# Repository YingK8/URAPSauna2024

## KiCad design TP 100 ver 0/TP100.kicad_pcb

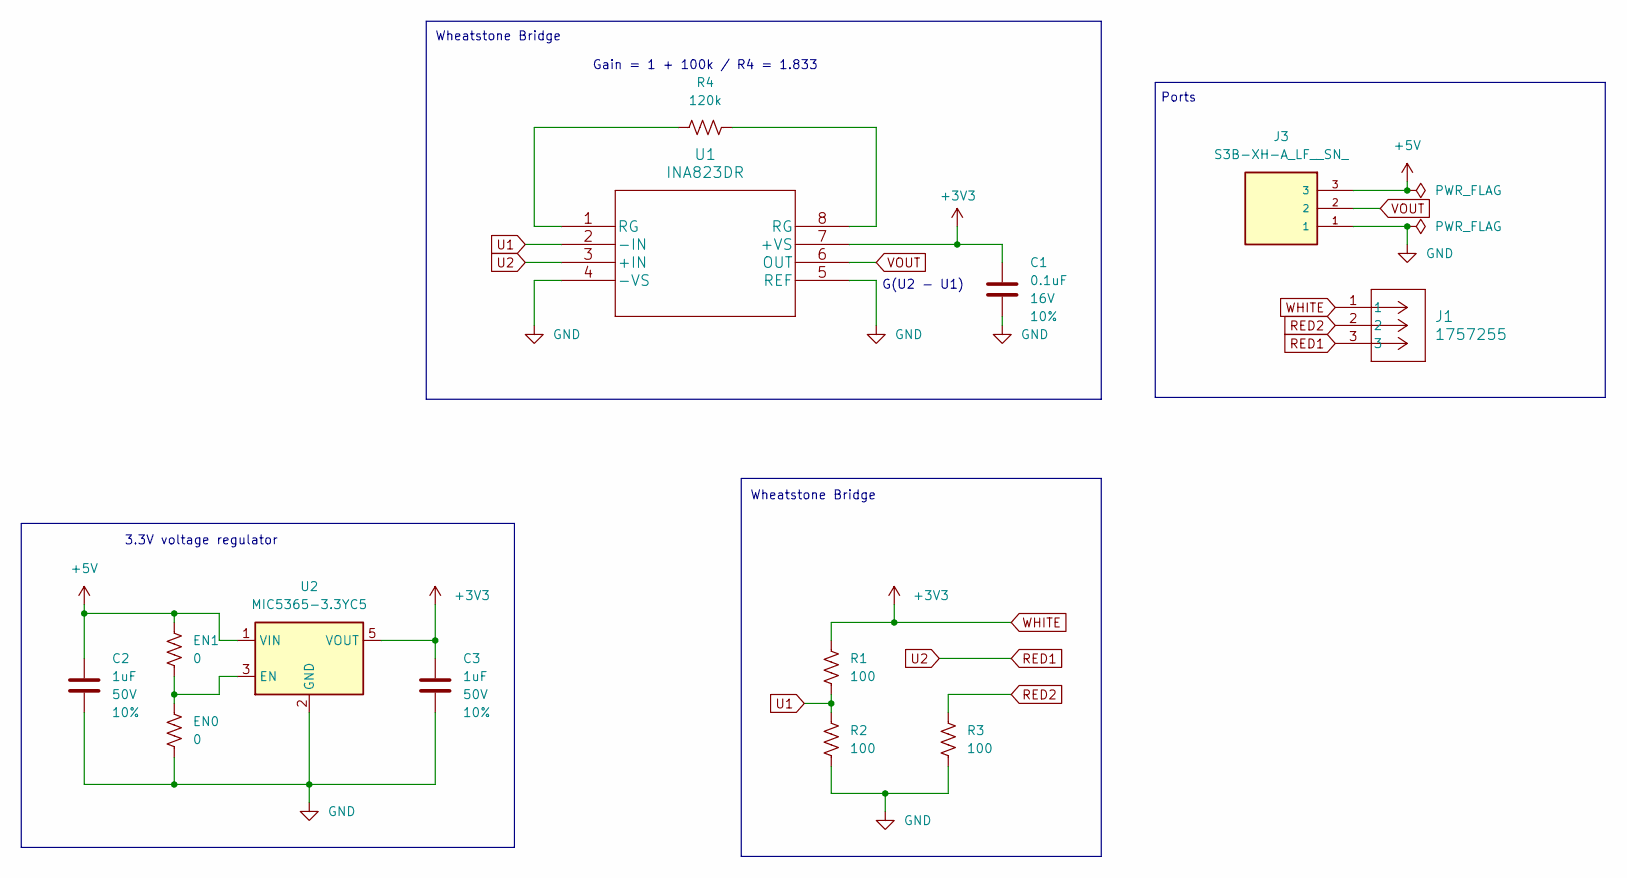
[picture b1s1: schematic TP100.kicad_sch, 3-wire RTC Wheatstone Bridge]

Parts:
C1: 0.1uF; C_0603_1608Metric_Pad1.08x0.95mm_HandSolder; Voltage 16V; Tolerance 10%
C2, C3: 1uF; C_0603_1608Metric_Pad1.08x0.95mm_HandSolder; Voltage 50V; Tolerance 10%
EN0, EN1: 0; C_0603_1608Metric_Pad1.08x0.95mm_HandSolder
J1: 1757255; PhoenixContact_MSTBA_2,5_3-G-5,08_1x03_P5.08mm_Horizontal
J3: S3B-XH-A_LF__SN_; JST_S3B-XH-A_LF__SN_; PARTREV N/A
R1, R2, R3: 100; R_0603_1608Metric_Pad0.98x0.95mm_HandSolder
R4: 120k; R_0603_1608Metric_Pad0.98x0.95mm_HandSolder
U1: INA823DR; INA823DT
U2: MIC5365-3.3YC5; SOT-353_SC-70-5_Handsoldering

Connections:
+5V: C2.1, EN1.2, J3.3, U2.1 (VIN)
GND: C1.2, C2.2, C3.2, EN0.1, J3.1, R2.2, R3.2, U1.4 (-VS), U1.5 (REF), U2.2 (GND)
unnamed: R4.1, U1.1 (RG)
unnamed: R4.2, U1.8 (RG)
unnamed: EN0.2, EN1.1, U2.3 (EN)
RED1: J1.3, U1.3 (+IN)
RED2: J1.2, R3.1
U1: R1.2, R2.1, U1.2 (-IN)
VOUT: J3.2, U1.6 (OUT)
WHITE: C1.1, C3.1, J1.1, R1.1, U1.7 (+VS), U2.5 (VOUT)

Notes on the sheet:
Wheatstone Bridge
Gain = 1 + 100k / R4 = 1.833
Ports
3.3V voltage regulator
G(U2 - U1)

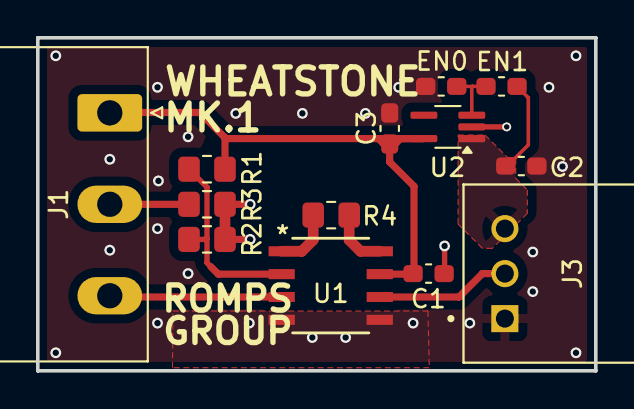
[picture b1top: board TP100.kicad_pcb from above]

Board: 2 copper layers, 31.0 x 18.5 mm, 13 parts (0 on the bottom side), 10 nets.

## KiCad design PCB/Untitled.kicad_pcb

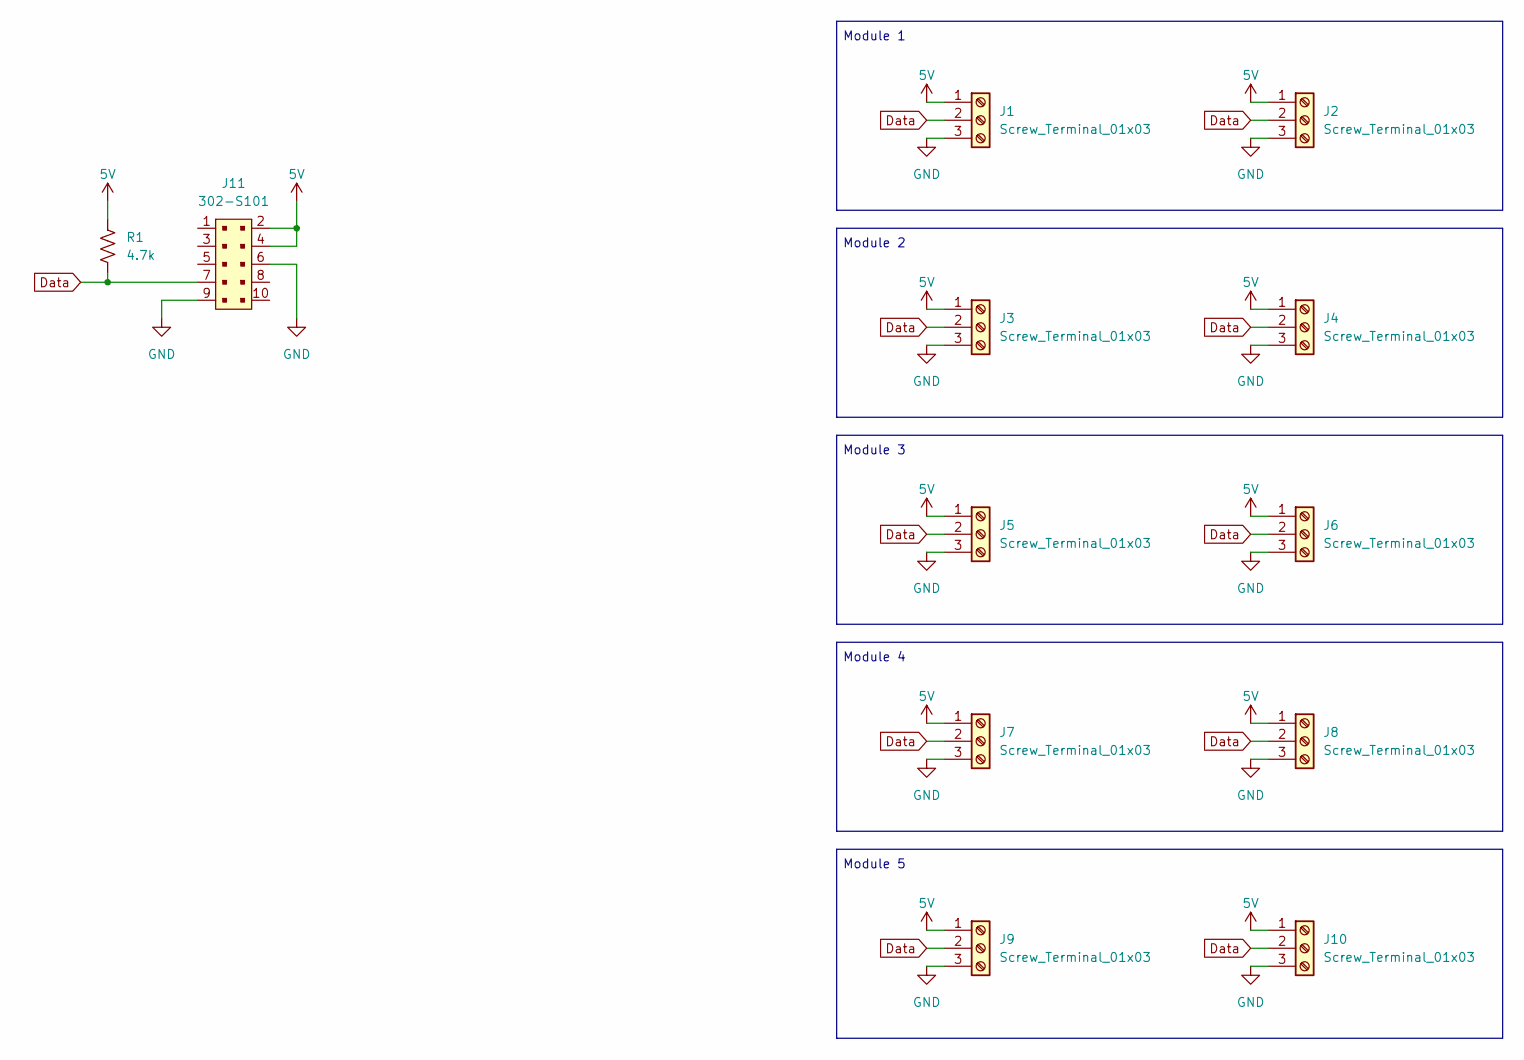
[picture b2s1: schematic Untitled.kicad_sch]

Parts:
J1, J2, J3, J4, J5, J6, J7, J8, J9, J10: Screw_Terminal_01x03; TerminalBlock_Xinya_XY308-2.54-3P_1x03_P2.54mm_Horizontal
J11: 302-S101; PinHeader_2x5_P2.54mm_Drill1.2mm; MPN 302-S101; Digi-Key_PN ED1543-ND
R1: 4.7k; R_Axial_DIN0207_L6.3mm_D2.5mm_P10.16mm_Horizontal

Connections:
5V: J1.1, J2.1, J3.1, J4.1, J5.1, J6.1, J7.1, J8.1, J9.1, J10.1, J11.2, J11.4, R1.1
Data: J1.2, J2.2, J3.2, J4.2, J5.2, J6.2, J7.2, J8.2, J9.2, J10.2, J11.7, R1.2
GND: J1.3, J2.3, J3.3, J4.3, J5.3, J6.3, J7.3, J8.3, J9.3, J10.3, J11.6, J11.9

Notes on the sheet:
Module 2
Module 3
Module 5
Module 4
Module 1

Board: 2 copper layers, 12 parts (0 on the bottom side), 3 nets, no tracks yet.

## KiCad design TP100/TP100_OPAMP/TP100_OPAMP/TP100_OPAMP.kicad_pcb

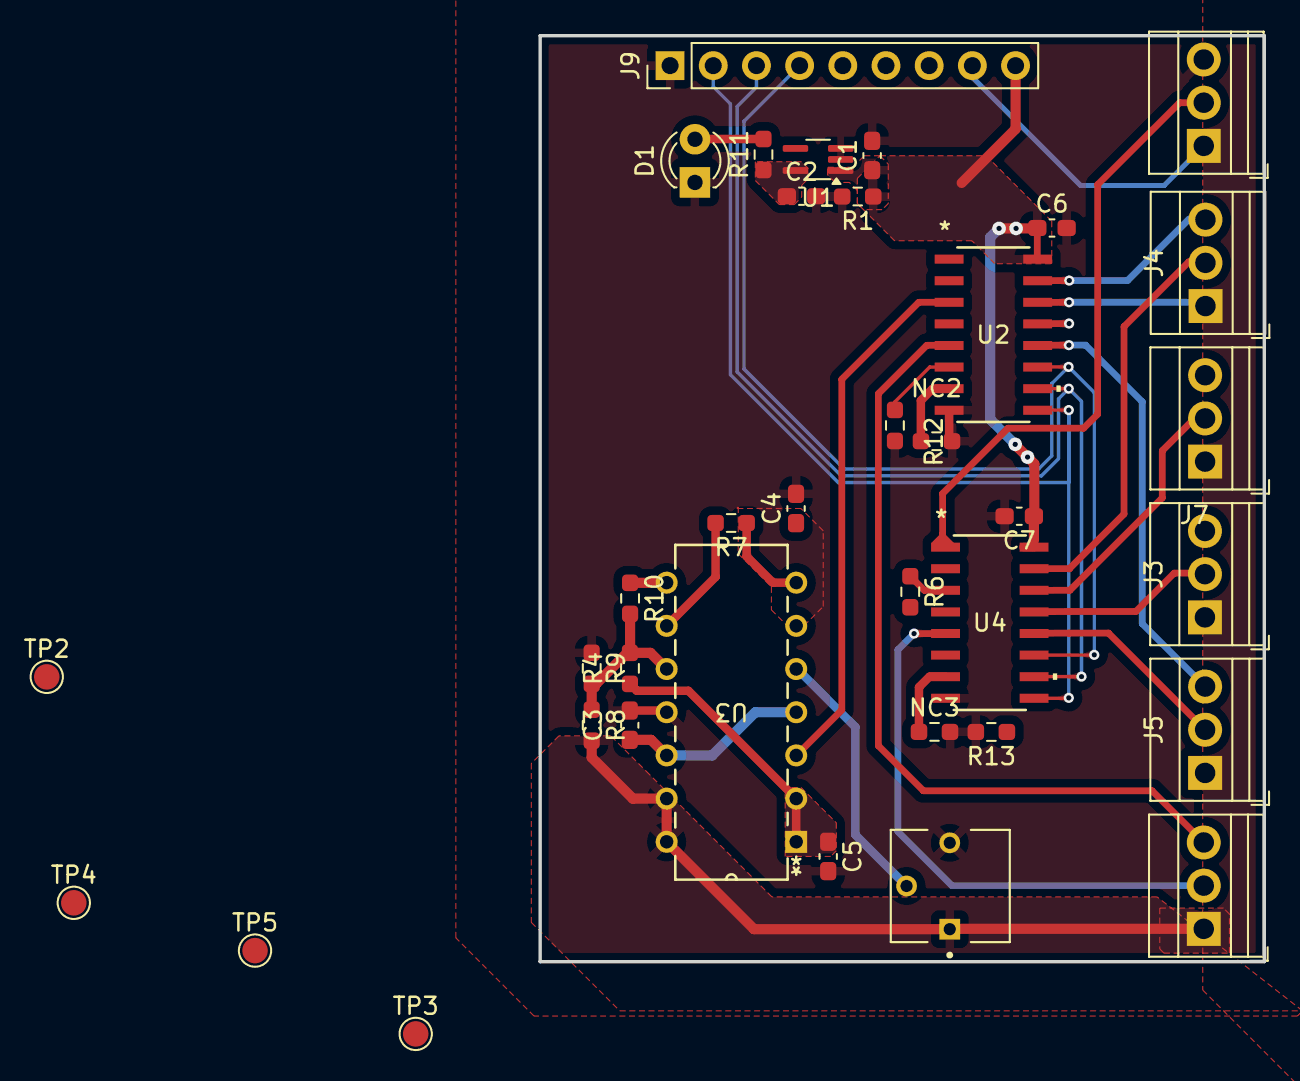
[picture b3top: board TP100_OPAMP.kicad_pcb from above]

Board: 2 copper layers, 42.6 x 54.5 mm, 36 parts (0 on the bottom side), 29 nets.

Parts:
C1, C2: 1uF; C_0603_1608Metric_Pad1.08x0.95mm_HandSolder
C3, C4, C5, C6, C7: 0.1uF; C_0603_1608Metric_Pad1.08x0.95mm_HandSolder
D1: LED; LED_D3.0mm
J2, J3, J4, J5, J6, J7: Screw_Terminal_01x03; TerminalBlock_Xinya_XY308-2.54-3P_1x03_P2.54mm_Horizontal
J9: Conn_01x09_Pin; PinHeader_1x09_P2.54mm_Vertical
NC2, NC3: 0; R_0603_1608Metric_Pad0.98x0.95mm_HandSolder
R1, R11: 100K; R_0603_1608Metric_Pad0.98x0.95mm_HandSolder
R4, R7, R8, R9, R10, R12, R13: 10K; R_0603_1608Metric_Pad0.98x0.95mm_HandSolder
R6: 100; R_0603_1608Metric_Pad0.98x0.95mm_HandSolder
TP2, TP3, TP4, TP5: TestPoint; TestPoint_Pad_D1.5mm
U1: MIC5365-3.3YC5; SOT-353_SC-70-5_Handsoldering
U2, U4: 74HC4051D; SOT109-1_NXP
U3: LM324N; N14
VR1: 3362P-1-103LF; TRIM_3362P-1-103LF

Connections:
+3V3: C2.1, C3.1, R11.1, U1.5 (VOUT), U3.4 (VCC), U3.12 (4IN+)
+5V: C1.1, C6.1, C7.1, J9.9, R1.1, TP2.1, U1.1 (VIN), U2.16 (VCC), U4.16 (VCC)
/EN: R12.1, R13.1, U2.6 (E*), U4.6 (E*)
/S0: J9.4, U2.11 (S0), U4.11 (S0)
/S1: J9.3, U2.10 (S1), U4.10 (S1)
/S2: J9.2, U2.9 (S2), U4.9 (S2)
/VEE: J9.5, NC2.1, NC3.1, U2.7 (VEE), U4.7 (VEE)
/V_IN_NEG: R7.2, U3.9 (3IN-)
/V_IN_POS: R4.2, R8.1, R9.2, R10.2, U3.10 (3IN+)
/V_OUT: R10.1, U3.8 (3OUT)
GND: C1.2, C2.2, C3.2, C4.2, C5.2, C6.2, C7.2, D1.1 (K), J6.3, J9.1, NC2.2, NC3.2, R1.2, R6.2, R9.1, R12.2, R13.2, TP4.1, U1.2 (GND), U1.3 (EN), U2.8 (GND), U3.11 (GND), U4.8 (GND), VR1.3
unnamed: D1.2 (A), R11.2
R01: J3.3, U2.13 (Y0)
R1: TP5.1, U2.3 (Z), U3.3 (1IN+)
R1_B: C5.1, J9.7, R4.1, U3.1 (1OUT), U3.2 (1IN-)
R02: J3.2, U4.13 (Y0)
R2: R6.1, U4.3 (Z)
R11: J2.3, U2.14 (Y1)
R12: J2.2, U4.14 (Y1)
R21: J4.3, U2.15 (Y2)
R22: J4.2, U4.15 (Y2)
R31: J5.3, U2.12 (Y3)
R32: J5.2, U4.12 (Y3)
R42: J6.2, U4.1 (Y4)
R51: J7.3, U2.5 (Y5)
R52: J7.2, U4.5 (Y5)
U: U3.5 (2IN+), VR1.2
U_B: C4.1, J9.6, R7.1, U3.6 (2IN-), U3.7 (2OUT)
W: J2.1, J3.1, J4.1, J5.1, J6.1, J7.1, J9.8, R8.2, TP3.1, U3.13 (4IN-), U3.14 (4OUT), VR1.1

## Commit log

2024-09-21 MODbus TCP WiFi prototype
2024-09-25 documentation tweaks
2024-09-26 replaced mock reading
2024-10-02 Added Temperature things
    PID cooling control
    One Wire thermometer reading
2024-10-02 the thermometer works!
2024-10-09 Modbus RTC and USART
2024-10-09 updated modbus reading method
2024-10-09 oneWire stuff
    Its just reading and printing the temperature for now (PID not working)
2024-10-09 Added timed measurements
2024-10-14 one Wire interface done theoretically
2024-10-15 added external save registry
2024-10-21 I did it [cool emoji]
2024-10-21 added KiCAD version of PCB
2025-03-26 sparkfun devboard
2025-03-26 changed to my arduino board
2025-05-01 past PCB designs
2025-05-01 organised better

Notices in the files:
parts and their libraries:
Copyright 2016 Accelerated Designs. All rights reserved.
